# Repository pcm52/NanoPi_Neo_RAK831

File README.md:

# NanoPi_Neo_RAK831
PCB to connect RAK831 to a NanoPi Neo

Interface has the following:
- optional Ublox GPS module with 1 PPS output to RAK831
- optional USB interface to allow easy configuration of GPS
- optional 128x32 i2c OLED display (at address 3C) 
- optional BMP280/BME280 temp/pressure/humidity sensor
- optional i2c header

More info here:

pcm52.com/2017/10/01/lorawan-gateway/

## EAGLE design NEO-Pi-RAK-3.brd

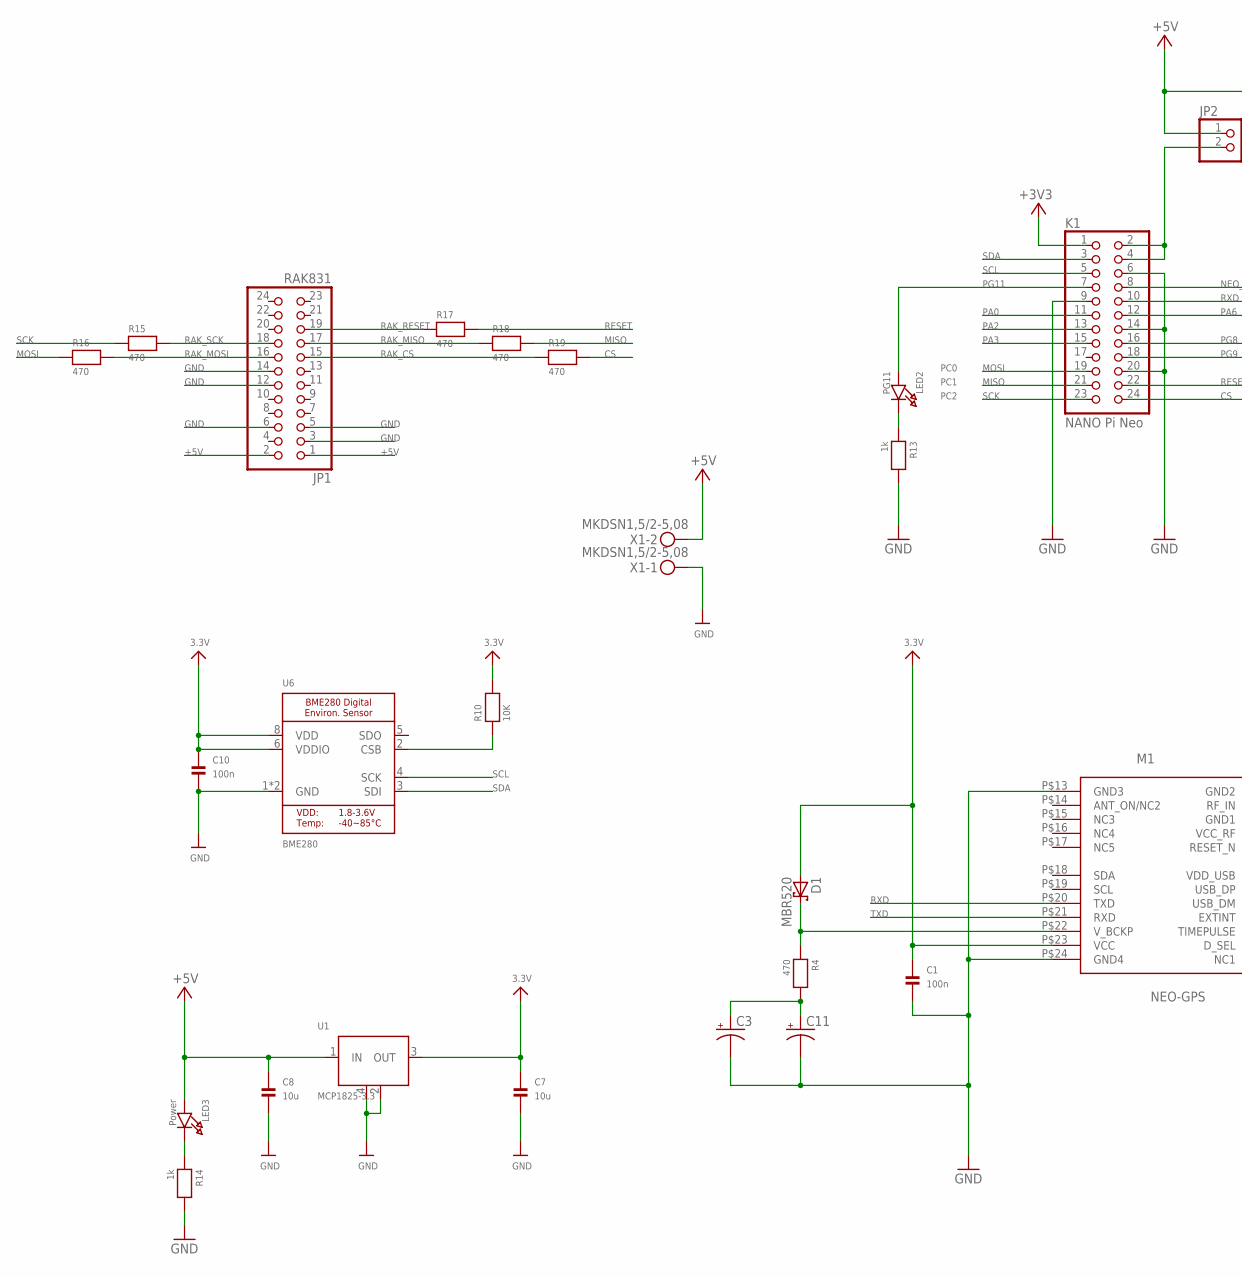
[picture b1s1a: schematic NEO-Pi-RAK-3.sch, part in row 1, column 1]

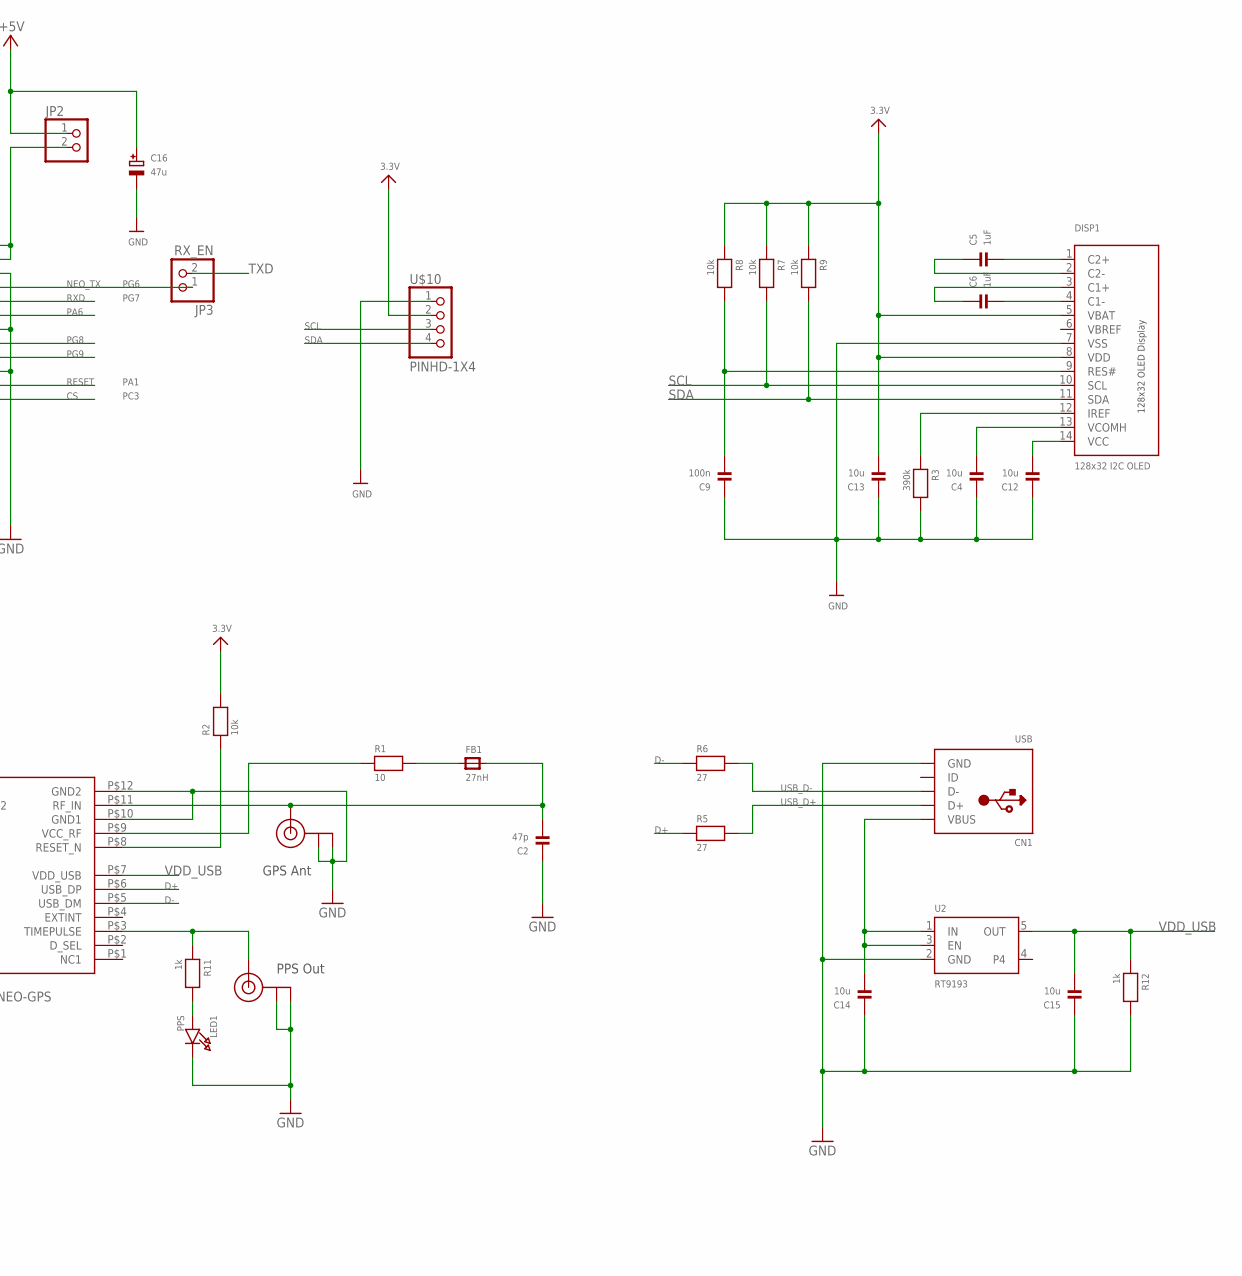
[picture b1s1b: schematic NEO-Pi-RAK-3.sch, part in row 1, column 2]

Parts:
C1, C9, C10: 100n; 0805
C2: 47p; 0805
C3: SUPERCAP; 414-VA5R
C4, C7, C8, C12, C13, C14, C15: 10u; 0805
C5, C6: 1uF; 0805
C11: SUPERCAP
C16: 47u; EIA3528-21/B-R
CN1: USB; USB-MINIB
D1: MBR520; SOD123
DISP1: 128x32 I2C OLED; 0.91-128X32-OLED-I2C
FB1: 27nH; 0805
JP1: RAK831; 2X12
JP2: PINHD-1X2; 1X02
JP3: RX_EN; 1X02
K1: NANO Pi Neo; 2X12
LED1: PPS; CHIPLED_0805
LED2: PG11; CHIPLED_0805
LED3: Power; CHIPLED_0805
M1: NEO-GPS; NEO_GPS
R1: 10; 0805
R2, R7, R8, R9: 10k; 0805
R3: 390k; 0805
R4, R15, R16, R17, R18, R19: 470; 0805
R5, R6: 27; 0805
R10: 10K; 0805
R11, R12, R13, R14: 1k; 0805
U1: MCP1825-3.3; UA78M05
U2: RT9193; SOT23-5
U6: BME280
U$1, U$2: U.FL
U$10: PINHD-1X4; 1X04-BIG
X1: MKDSN1,5/2-5,08

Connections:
3.3V: C1.1, C7.1, C10.1, C13.2, D1.A, DISP1.5 (VBAT), DISP1.8 (VDD), M1.P$23 (VCC), R2.2, R7.1, R8.1, R9.1, R10.2, U1.3 (OUT), U6.6 (VDDIO), U6.8 (VDD), U$10.2
+3V3: K1.1
+5V: C8.1, C16.+, JP1.1, JP1.2, JP2.1, LED3.A, U1.1 (IN), X1.2
CS: K1.24, R19.2
D+: M1.P$6 (USB_DP), R5.1
D-: M1.P$5 (USB_DM), R6.1
GND: C1.2, C2.1, C3.-, C4.1, C7.2, C8.2, C9.1, C10.2, C11.P$2 (-), C12.1, C13.1, C14.1, C15.1, C16.-, CN1.GND, DISP1.7 (VSS), JP1.3, JP1.5, JP1.6, JP1.12, JP1.14, K1.6, K1.9, K1.14, K1.20, LED1.C, M1.P$10 (GND1), M1.P$12 (GND2), M1.P$13 (GND3), M1.P$24 (GND4), R3.2, R12.2, R13.2, R14.2, U1.2 (COMMON1), U1.4 (COMMON2), U2.2 (GND), U6.1 (GND), U6.7 (GND), U$1.P$1 (GND), U$1.P$2 (GND), U$2.P$1 (GND), U$2.P$2 (GND), U$10.1, X1.1
MISO: K1.21, R18.2
MOSI: K1.19, R16.1
unnamed: JP2.2, K1.2, K1.4
unnamed: M1.P$3 (TIMEPULSE), R11.1, U$2.P$3 (SIGNAL)
unnamed: C2.2, FB1.2, M1.P$11 (RF_IN), U$1.P$3 (SIGNAL)
unnamed: FB1.1, R1.2
unnamed: C12.2, DISP1.14 (VCC)
unnamed: M1.P$9 (VCC_RF), R1.1
unnamed: M1.P$8 (RESET_N), R2.1
unnamed: D1.C, M1.P$22 (V_BCKP), R4.1
unnamed: C3.+, C11.P$1 (+), R4.2
unnamed: C4.2, DISP1.13 (VCOMH)
unnamed: LED1.A, R11.2
unnamed: C5.2, DISP1.1 (C2+)
unnamed: C6.2, DISP1.4 (C1-)
unnamed: C6.1, DISP1.3 (C1+)
unnamed: C5.1, DISP1.2 (C2-)
unnamed: C14.2, CN1.VBUS, U2.1 (IN), U2.3 (EN)
unnamed: DISP1.12 (IREF), R3.1
unnamed: LED3.C, R14.1
unnamed: R10.1, U6.2 (CSB)
unnamed: LED2.C, R13.1
NEO_TX: JP3.1, K1.8
PA0: K1.11
PA2: K1.13
PA3: K1.15
PA6: K1.12
PG8: K1.16
PG9: K1.18
PG11: K1.7, LED2.A
RAK_CS: JP1.15, R19.1
RAK_MISO: JP1.17, R18.1
RAK_MOSI: JP1.16, R16.2
RAK_RESET: JP1.19, R17.1
RAK_SCK: JP1.18, R15.2
RESET: K1.22, R17.2
RST_OLED: C9.2, DISP1.9 (RES#), R8.2
RXD: K1.10, M1.P$20 (TXD)
SCK: K1.23, R15.1
SCL: DISP1.10 (SCL), K1.5, R7.2, U6.4 (SCK), U$10.3
SDA: DISP1.11 (SDA), K1.3, R9.2, U6.3 (SDI), U$10.4
TXD: JP3.2, M1.P$21 (RXD)
USB_D+: CN1.D+, R5.2
USB_D-: CN1.D-, R6.2
VBREF: DISP1.6 (VBREF)
VDD_USB: C15.2, M1.P$7 (VDD_USB), R12.1, U2.5 (OUT)

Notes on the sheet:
PA1
PC3
PC0
PC1
PC2
PG6
PG7
GPS Ant
PPS Out

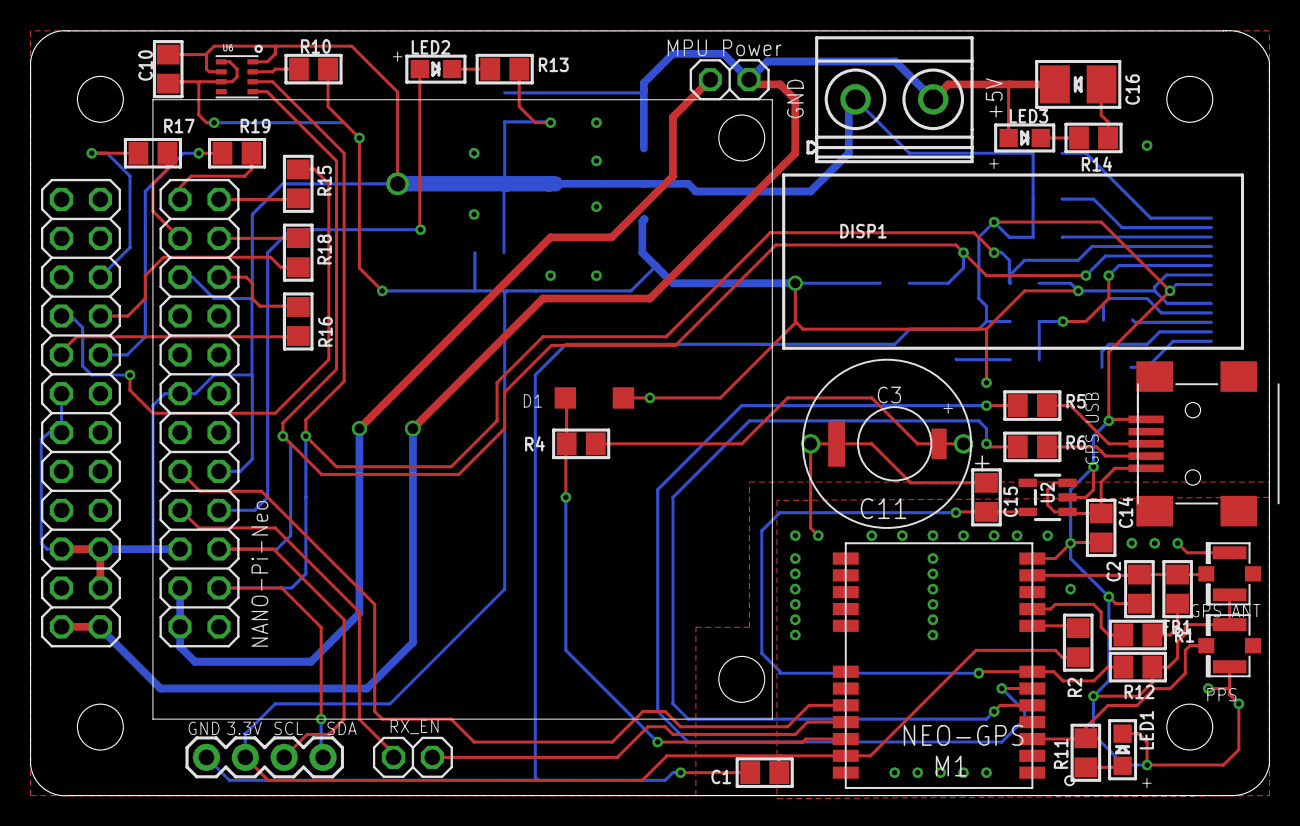
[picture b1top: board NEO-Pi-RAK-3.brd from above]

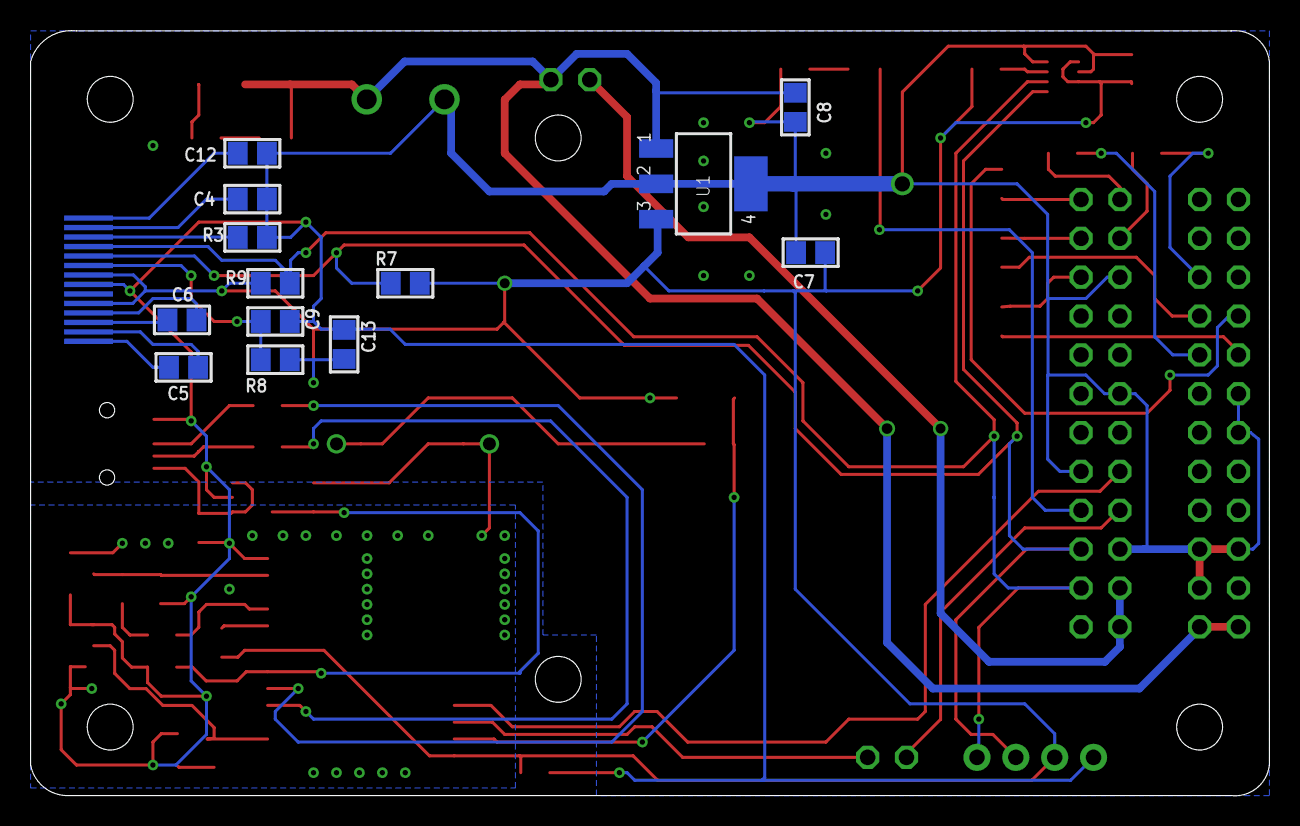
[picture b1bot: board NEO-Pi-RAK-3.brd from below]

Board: 2 copper layers, 81.0 x 50.0 mm, 54 parts (13 on the bottom side), 45 nets.

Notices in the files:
parts and their libraries:
microbuilder: This work is placed in the public domain, and may be freely used for commercial and non-commercial work with the following conditions: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
